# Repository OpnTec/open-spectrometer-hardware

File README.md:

# DIY Analytics Open Source Spectrometer

This repository provides hardware schematics and list of materials for the open spectrometer project to enable practitioners, students and citizen scientists to collect data with their spectrometer and have a good and fun learning experience. The open spectrometer project consists of a web cam, simple lasercut parts, battery casing and a suitable LED lightning component. The spectrometer connects to a computer via USB, where the user can run the scripts provided in this repository to run experiments and take measurements. Enjoy!

A transparent version of the spectrometer for explanation purposes.

## Open Science and Goals

By definition science should be open and reproducible. So, the outcome of an experiment can be verified by anyone. Unfortunately today this is not always the case. In order to be able to verify experiments all components used should be openly accessible. This includes the software and hardware of scientific instruments. Our spectrometer project follows this path. By giving access to all layers of the device used in a scientific experiment users can develop a deep understanding how scientific measurements are taken and practitioners are able to critically understand the limitations of the particular instrument.

The spectrometer consists of a set of materials designed to be available and affordable anywhere in the world. The design's focus is to promote education about spectrometry and analytical chemistry, with the goal of empowering, stimulating and encouraging individuals to learn about their environment applying scientific methodologies. Furthermore, the goal of the tool is to enable practitioners to study open design, scientific programming, physics and to reflect about reproducibility in scientific practices.

## Communication

The spectrometer community is still small. There are overlaps with the Pocket Science Lab team. To stay connected with different community members we continue to use the PSLab Gitter channel for the beginning. We will set up a dedicated channel once the project is more established. Please join us here:
* [Pocket Science Channel](https://gitter.im/fossasia/pslab)

## Features and Implementation Status

- The bill of materials is available in the /components folder.
- The design files for the lasercut files are available in the /schematics folder.

The camera component of the spectrometer in transparent casing.

Roadmap:

- improve the design of the wooden part holding the camera
- redesign the light side, in order to allow CFL light coming in without disassembling the whole spectrometer
- write a script that allows the user to control the spactrometer with a simple offline device
- reduce the size to fit in one 25x50cm board

## Software

To get the data from the spetrometer device practitioners can use the spectrometer Python scripts available in the project. 

## Contributors

Alessandro Volpato is the creator of the project. The work was done by merging concepts of the [Public Lab Spectrometer](https://publiclab.org/notes/abdul/10-13-2016/desktop-spectrometry-starter-kit-3-0-instructions), 
the [GaudiLabs spectrometer](http://www.gaudi.ch/GaudiLabs/?page_id=328) and creating new design features to simplify the assembly of a lasercut spetrometer.

## License

The repository is licenced under CERN Open Hardware Licence v1.2

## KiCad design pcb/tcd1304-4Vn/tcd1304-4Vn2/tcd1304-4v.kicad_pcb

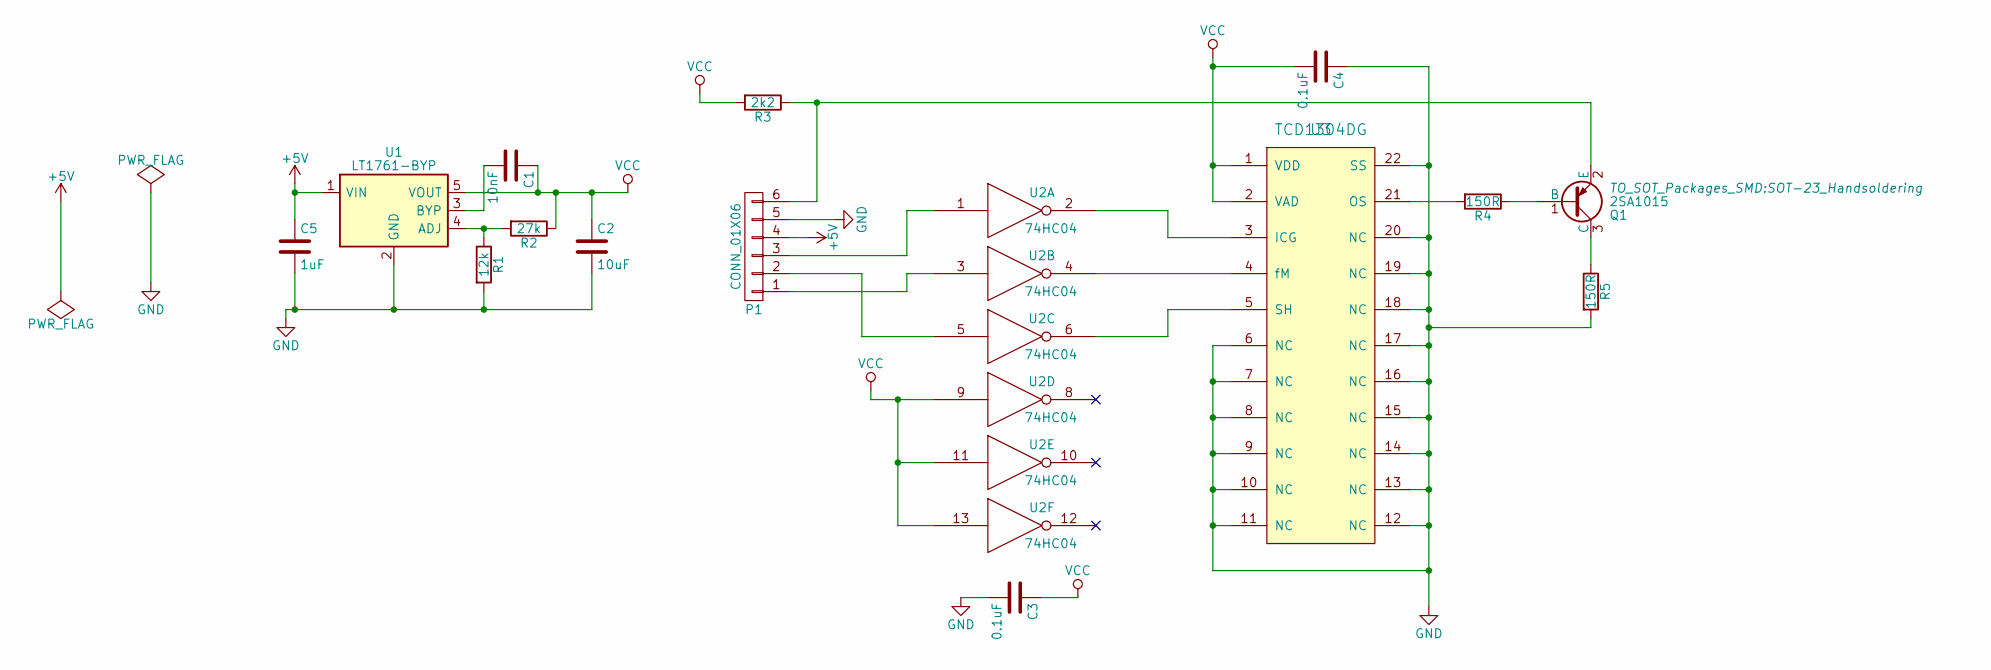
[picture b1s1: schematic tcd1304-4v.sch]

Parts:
C1: 10nF; C_0805
C2: 10uF; C_1206
C3, C4: 0.1uF; C_0805
C5: 1uF; C_0805
P1: CONN_01X06; Pin_Header_Straight_1x06
Q1: 2SA1015; SOT-23_Handsoldering
R1: 12k; C_0805
R2: 27k; C_0805
R3: 2k2; C_0805
R4, R5: 150R; C_0805
U1: LT1761-BYP; SOT-23-5-handsoldering
U2: 74HC04; SOIC-14_3.9x8.7mm_Pitch1.27mm
U3: TCD1304DG; DIP-22_W10.16mm

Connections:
+5V: C5.1, P1.4, U1.1 (VIN)
GND: C2.2, C3.2, C4.1, C5.2, P1.5, R1.2, R5.2, U1.2 (GND), U2.7 (GND), U3.6 (NC), U3.7 (NC), U3.8 (NC), U3.9 (NC), U3.10 (NC), U3.11 (NC), U3.12 (NC), U3.13 (NC), U3.14 (NC), U3.15 (NC), U3.16 (NC), U3.17 (NC), U3.18 (NC), U3.19 (NC), U3.20 (NC), U3.22 (SS)
unnamed: C1.2, U1.3 (BYP)
unnamed: P1.1, U2.3
unnamed: P1.2, U2.5
unnamed: P1.3, U2.1
unnamed: P1.6, Q1.2 (E), R3.1
unnamed: Q1.1 (B), R4.1
unnamed: Q1.3 (C), R5.1
unnamed: R1.1, R2.2, U1.4 (ADJ)
unnamed: R4.2, U3.21 (OS)
unnamed: U2.2, U3.3 (ICG)
unnamed: U2.4, U3.4 (fM)
unnamed: U2.6, U3.5 (SH)
VCC: C1.1, C2.1, C3.1, C4.2, R2.1, R3.2, U1.5 (VOUT), U2.9, U2.11, U2.13, U2.14 (VCC), U3.1 (VDD), U3.2 (VAD)

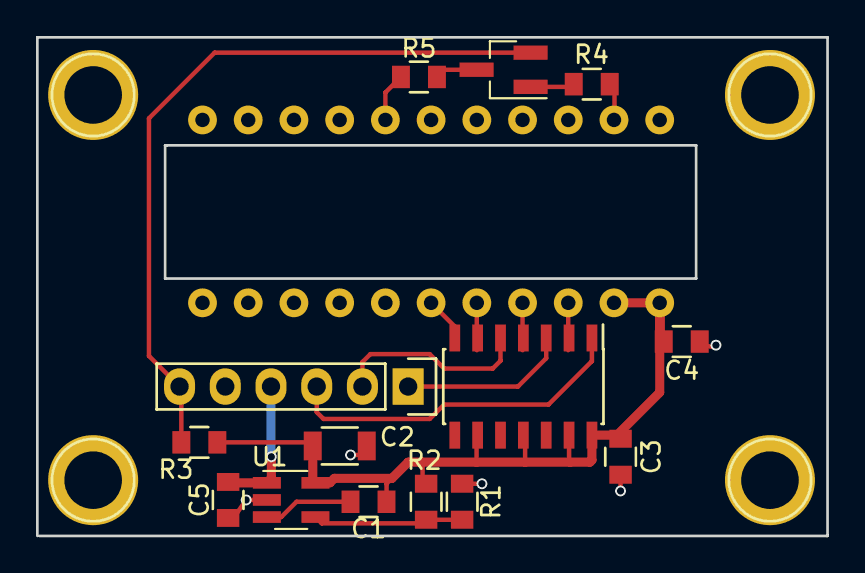
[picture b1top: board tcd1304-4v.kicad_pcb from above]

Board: 2 copper layers, 43.9 x 27.7 mm, 15 parts (1 on the bottom side), 15 nets.

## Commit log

2017-09-16 ots18
2017-09-23 Create CNAME
2017-09-23 Update CNAME
2017-10-12 address
2017-10-12 logo
2017-10-12 details
2017-10-21 date
2017-11-02 event
2017-11-09 team details
2017-11-10 index update
2017-11-14 linked speakers link, was not working earlier
2018-08-23 Update Index file
2018-08-24 Update Index
2018-08-25 Update map
2018-08-25 Update schedule
2018-08-25 Update schedule layout
2018-08-31 clean up
2018-09-06 Add hotels information
2018-09-06 Add ticket page
2018-10-18 Add qixiang
2018-10-18 Add photos speakers
2018-11-14 cleanup
2018-11-14 schedule
2018-11-14 tweets
2018-11-15 schedule update
2018-11-16 additional info
2018-11-17 hotels
2018-11-24 button
2019-03-27 2019
2019-03-27 image
2019-09-18 Remove last year speakers
2019-09-20 Update ticket links
2019-09-20 Update URLs
2020-06-11 added images
2020-06-12 updated docs, and reorganized repo
2020-06-12 add images
2020-06-14 A4 schematics
2021-03-05 spectrometer v2
2021-03-08 docs
